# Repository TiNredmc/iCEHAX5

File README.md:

# iCEHAX5 FPGA 

iCEHAX5 FPGA is a bare-minimum and open-source FPGA development board based on iCE5LP1K, iCE5LP2K, or iCE5LP4K. With the help of the iCEBlaster. Drag-and-Drop programming made it easy. Compatible with Windows, Mac OS and Linux without any additional drivers. 

# iCEHAX5 Hardware Specifications 
- iCE5LP1K or iCE5LP2K or iCE5LP4K (QFN48 package; -SG48).
    - 1100 or 2048 or 3520 Programmable Logic Cells (PLBs).
    - 64 or 80 or 80 kBit Block RAM (BRAM). 
    - Single programmable Phase Lock Loop (PLL).
    - 2 or 4 or 4 Multiplier And Accumulator DSP blocks (MAC).
    - 1 or 2 or 2 I2C Hard IPs.
    - 1 or 2 or 2 SPI Hard IPs.
    - 10Khz and 48MHz internal Oscillator 
- 37 Usable Pins
    - 34 User accessible PIOs
    - 3 Open Drain Only pins for RGB LED.
- iCEBlaster USB Drag and Drop programmer.
    - Based on STM32F042F4P6 or STM32F042F6P6.
    - Bitstream storage : BR24G1MFJ 128kByte I2C EEPROM (I know it sucks, but it work!).
    - Bitstream transfer to the FPGA over SPI bus 
- On board LED status for iCEBlaster.

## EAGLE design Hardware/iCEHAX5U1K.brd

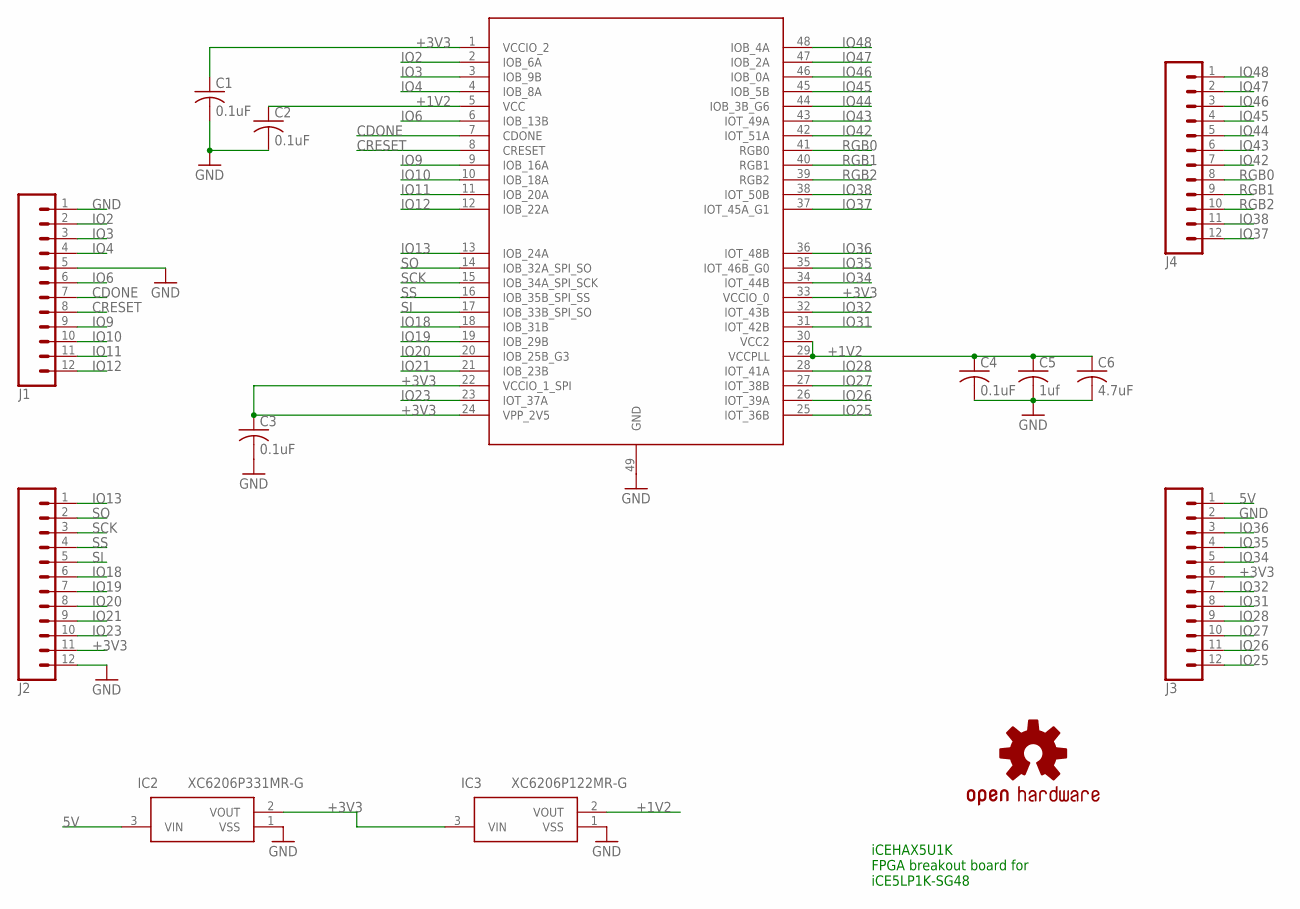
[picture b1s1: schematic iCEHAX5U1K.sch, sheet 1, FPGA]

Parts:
C1, C2, C3, C4: 0.1uF; C0603
C5: 1uf; C0603
C6: 4.7uF; C0603
IC1: ICE5LP1K-SG48; QFN50P700X700X100-48T535N
IC2: XC6206P331MR-G; SOT95P280X130-3N
IC3: XC6206P122MR-G; SOT95P280X130-3N
J1, J2, J3, J4: CONN_12NO_SILK; 1X12_NO_SILK
LOGO1: OSHW-LOGOMINI; OSHW-LOGO-MINI

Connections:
5V: IC2.3 (VIN), J3.1; also elsewhere on the board
+1V2: C2.1, C4.1, C5.1, C6.1, IC1.5 (VCC), IC1.29 (VCCPLL), IC1.30 (VCC2), IC3.2 (VOUT)
+3V3: C1.1, C3.1, IC1.1 (VCCIO_2), IC1.22 (VCCIO_1_SPI), IC1.24 (VPP_2V5), IC1.33 (VCCIO_0), IC2.2 (VOUT), IC3.3 (VIN), J2.11, J3.6; also elsewhere on the board
CDONE: IC1.7 (CDONE), J1.7
CRESET: IC1.8 (CRESET), J1.8; also elsewhere on the board
GND: C1.2, C2.2, C3.2, C4.2, C5.2, C6.2, IC1.49 (GND), IC2.1 (VSS), IC3.1 (VSS), J1.1, J1.5, J2.12, J3.2; also elsewhere on the board
IO2: IC1.2 (IOB_6A), J1.2
IO3: IC1.3 (IOB_9B), J1.3
IO4: IC1.4 (IOB_8A), J1.4
IO6: IC1.6 (IOB_13B), J1.6
IO9: IC1.9 (IOB_16A), J1.9
IO10: IC1.10 (IOB_18A), J1.10
IO11: IC1.11 (IOB_20A), J1.11
IO12: IC1.12 (IOB_22A), J1.12
IO13: IC1.13 (IOB_24A), J2.1
IO18: IC1.18 (IOB_31B), J2.6
IO19: IC1.19 (IOB_29B), J2.7
IO20: IC1.20 (IOB_25B_G3), J2.8
IO21: IC1.21 (IOB_23B), J2.9
IO23: IC1.23 (IOT_37A), J2.10
IO25: IC1.25 (IOT_36B), J3.12
IO26: IC1.26 (IOT_39A), J3.11
IO27: IC1.27 (IOT_38B), J3.10
IO28: IC1.28 (IOT_41A), J3.9
IO31: IC1.31 (IOT_42B), J3.8
IO32: IC1.32 (IOT_43B), J3.7
IO34: IC1.34 (IOT_44B), J3.5
IO35: IC1.35 (IOT_46B_G0), J3.4
IO36: IC1.36 (IOT_48B), J3.3
IO37: IC1.37 (IOT_45A_G1), J4.12
IO38: IC1.38 (IOT_50B), J4.11
IO42: IC1.42 (IOT_51A), J4.7
IO43: IC1.43 (IOT_49A), J4.6
IO44: IC1.44 (IOB_3B_G6), J4.5
IO45: IC1.45 (IOB_5B), J4.4
IO46: IC1.46 (IOB_0A), J4.3
IO47: IC1.47 (IOB_2A), J4.2
IO48: IC1.48 (IOB_4A), J4.1
RGB0: IC1.41 (RGB0), J4.8
RGB1: IC1.40 (RGB1), J4.9
RGB2: IC1.39 (RGB2), J4.10
SCK: IC1.15 (IOB_34A_SPI_SCK), J2.3; also elsewhere on the board
SI: IC1.17 (IOB_33B_SPI_SO), J2.5; also elsewhere on the board
SO: IC1.14 (IOB_32A_SPI_SO), J2.2; also elsewhere on the board
SS: IC1.16 (IOB_35B_SPI_SS), J2.4; also elsewhere on the board

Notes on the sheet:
iCEHAX5U1K FPGA breakout board for iCE5LP1K-SG48

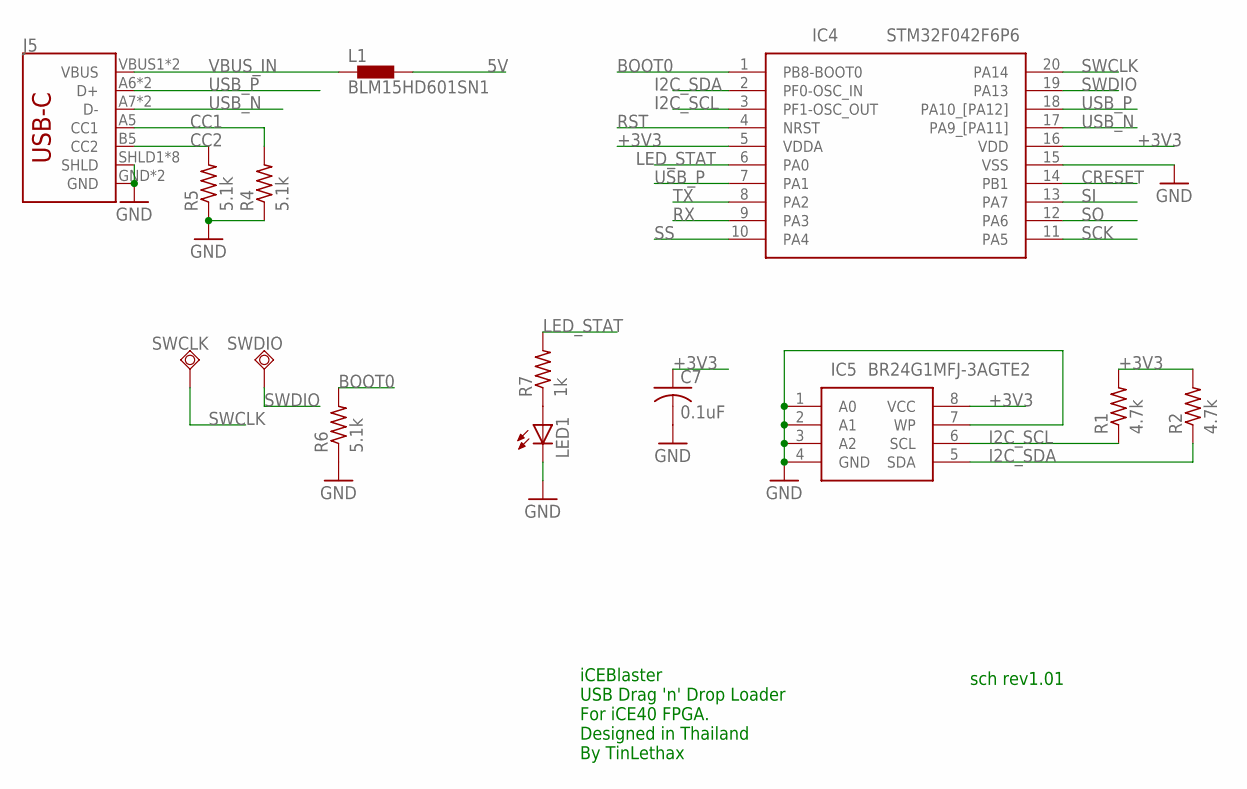
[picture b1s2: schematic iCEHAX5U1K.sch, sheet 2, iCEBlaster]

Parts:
C7: 0.1uF; C0603
IC4: STM32F042F6P6; SOP65P640X120-20N
IC5: BR24G1MFJ-3AGTE2; SOP126P620X150-8N
J5: SPARKFUN-CONNECTORS_USB_C16PIN; SPARKFUN-CONNECTORS_USB-C-16P
L1: BLM15HD601SN1; 0402
LED1: LEDCHIP-LED0603; CHIP-LED0603
R1, R2: 4.7k; R0603
R4, R5, R6: 5.1k; R0603
R7: 1k; R0603
SWCLK: TPSQTP15SQ; TP15SQ
SWDIO: TPSQTP15SQ; TP15SQ

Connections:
5V: L1.2; also elsewhere on the board
+3V3: C7.1, IC4.5 (VDDA), IC4.16 (VDD), IC5.8 (VCC), R1.2, R2.2; also elsewhere on the board
BOOT0: IC4.1 (PB8-BOOT0), R6.2
CC1: J5.A5 (CC1), R4.2
CC2: J5.B5 (CC2), R5.2
CRESET: IC4.14 (PB1); also elsewhere on the board
GND: C7.2, IC4.15 (VSS), IC5.1 (A0), IC5.2 (A1), IC5.3 (A2), IC5.4 (GND), IC5.7 (WP), J5.GND, J5.GND2 (GND), J5.SHLD1 (SHLD), J5.SHLD2 (SHLD), J5.SHLD3 (SHLD), J5.SHLD4 (SHLD), J5.SHLD5 (SHLD), J5.SHLD6 (SHLD), J5.SHLD7 (SHLD), J5.SHLD8 (SHLD), LED1.C, R4.1, R5.1, R6.1; also elsewhere on the board
I2C_SCL: IC4.3 (PF1-OSC_OUT), IC5.6 (SCL), R1.1
I2C_SDA: IC4.2 (PF0-OSC_IN), IC5.5 (SDA), R2.1
LED: LED1.A, R7.1
LED_STAT: IC4.6 (PA0), R7.2
RST: IC4.4 (NRST)
RX: IC4.9 (PA3)
SCK: IC4.11 (PA5); also elsewhere on the board
SI: IC4.13 (PA7); also elsewhere on the board
SO: IC4.12 (PA6); also elsewhere on the board
SS: IC4.10 (PA4); also elsewhere on the board
SWCLK: IC4.20 (PA14), SWCLK.TP
SWDIO: IC4.19 (PA13), SWDIO.TP
TX: IC4.8 (PA2)
USB_N: IC4.17 (PA9_[PA11]), J5.A7 (D-), J5.B7 (D-)
USB_P: IC4.7 (PA1), IC4.18 (PA10_[PA12]), J5.A6 (D+), J5.B6 (D+)
VBUS_IN: J5.VBUS1 (VBUS), J5.VBUS2 (VBUS), L1.1

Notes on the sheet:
iCEBlaster USB Drag 'n' Drop Loader For iCE40 FPGA. Designed in Thailand By TinLethax
sch rev1.01

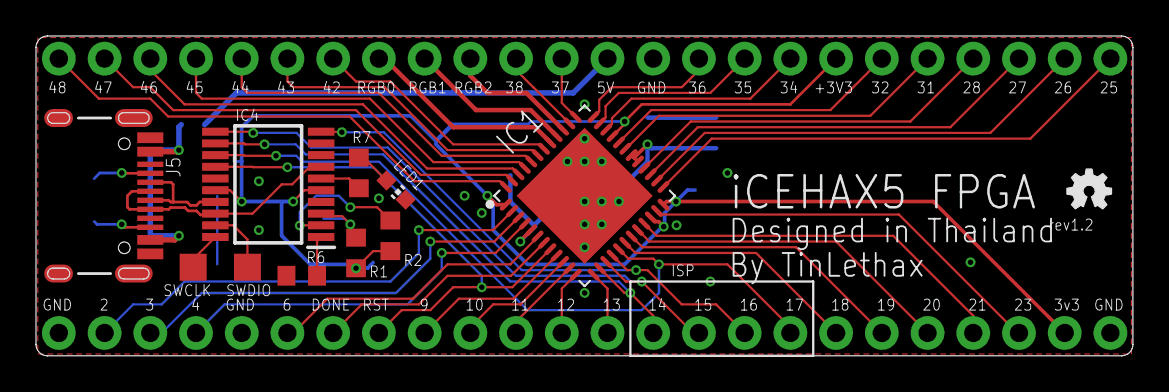
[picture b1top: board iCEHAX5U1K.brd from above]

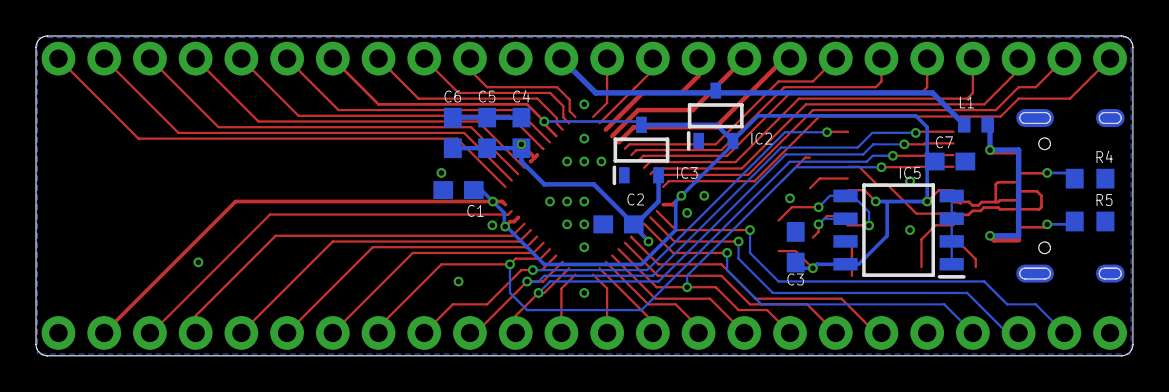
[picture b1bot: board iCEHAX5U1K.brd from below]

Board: 2 copper layers, 60.9 x 17.8 mm, 28 parts (13 on the bottom side), 57 nets.

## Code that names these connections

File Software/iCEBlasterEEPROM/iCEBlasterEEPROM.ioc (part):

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Mcu.Name=STM32F042F6Px
Mcu.Package=TSSOP20
Mcu.UserName=STM32F042F6Px
PA0.GPIOParameters=GPIO_Label
PA0.GPIO_Label=LED_STAT
PA0.Signal=GPIO_Output
PA1.GPIOParameters=PinState,GPIO_PuPd,GPIO_Label,GPIO_ModeDefaultOutputPP
PA1.GPIO_Label=USB_EN
PA1.GPIO_ModeDefaultOutputPP=GPIO_MODE_OUTPUT_OD
PA1.GPIO_PuPd=GPIO_NOPULL
PA1.PinState=GPIO_PIN_SET
PA1.Signal=GPIO_Output
PA11.Mode=Device
PA11.Signal=USB_DM
PA12.Mode=Device
PA12.Signal=USB_DP
PA13.Mode=Serial_Wire
PA13.Signal=SYS_SWDIO
PA14.Mode=Serial_Wire
PA14.Signal=SYS_SWCLK
PA4.GPIOParameters=GPIO_Label
PA4.GPIO_Label=SPI1_CE
PA4.Signal=GPIO_Output
PA5.Mode=Full_Duplex_Master
PA5.Signal=SPI1_SCK
PA6.Mode=Full_Duplex_Master
PA6.Signal=SPI1_MISO
PA7.Mode=Full_Duplex_Master
PA7.Signal=SPI1_MOSI
PB1.GPIOParameters=GPIO_Label
PB1.GPIO_Label=CRESET
PB1.Signal=GPIO_Output
PF0-OSC_IN.Mode=I2C
PF0-OSC_IN.Signal=I2C1_SDA
PF1-OSC_OUT.Mode=I2C
PF1-OSC_OUT.Signal=I2C1_SCL
RCC.SYSCLKFreq_VALUE=48000000
RCC.SYSCLKSource=RCC_SYSCLKSOURCE_HSI48
board=custom

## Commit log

2023-06-20 Initial.
2023-06-20 Create LICENSE
2023-06-20 Added Board pic.
2023-06-20 Added Image to README.
2023-06-22 Top PIO Bank design issue fixed. - Top PIO Bank (Pin 25 and up) was missing the VCC_IO rail due to confusion of pin 33.

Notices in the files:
parts and their libraries:
SparkFun-Connectors: Licensing: Creative Commons ShareAlike 4.0 International - https://creativecommons.org/licenses/by-sa/4.0
